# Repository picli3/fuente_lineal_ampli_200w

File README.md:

# fuente_lineal_ampli_200w

Fuente lineal diseñada para alimentar un amplificador de 200 W, con enfoque en robustez y compatibilidad con etapas de audio de potencia.

## Qué incluye
- esquemáticos o archivos de diseño en KiCad
- PCB o documentación asociada
- base reutilizable para análisis, fabricación o mejora del proyecto

## Propósito general
Este repositorio busca concentrar el diseño de hardware del proyecto en un formato editable y reutilizable, facilitando pruebas, documentación y futuras iteraciones del circuito.

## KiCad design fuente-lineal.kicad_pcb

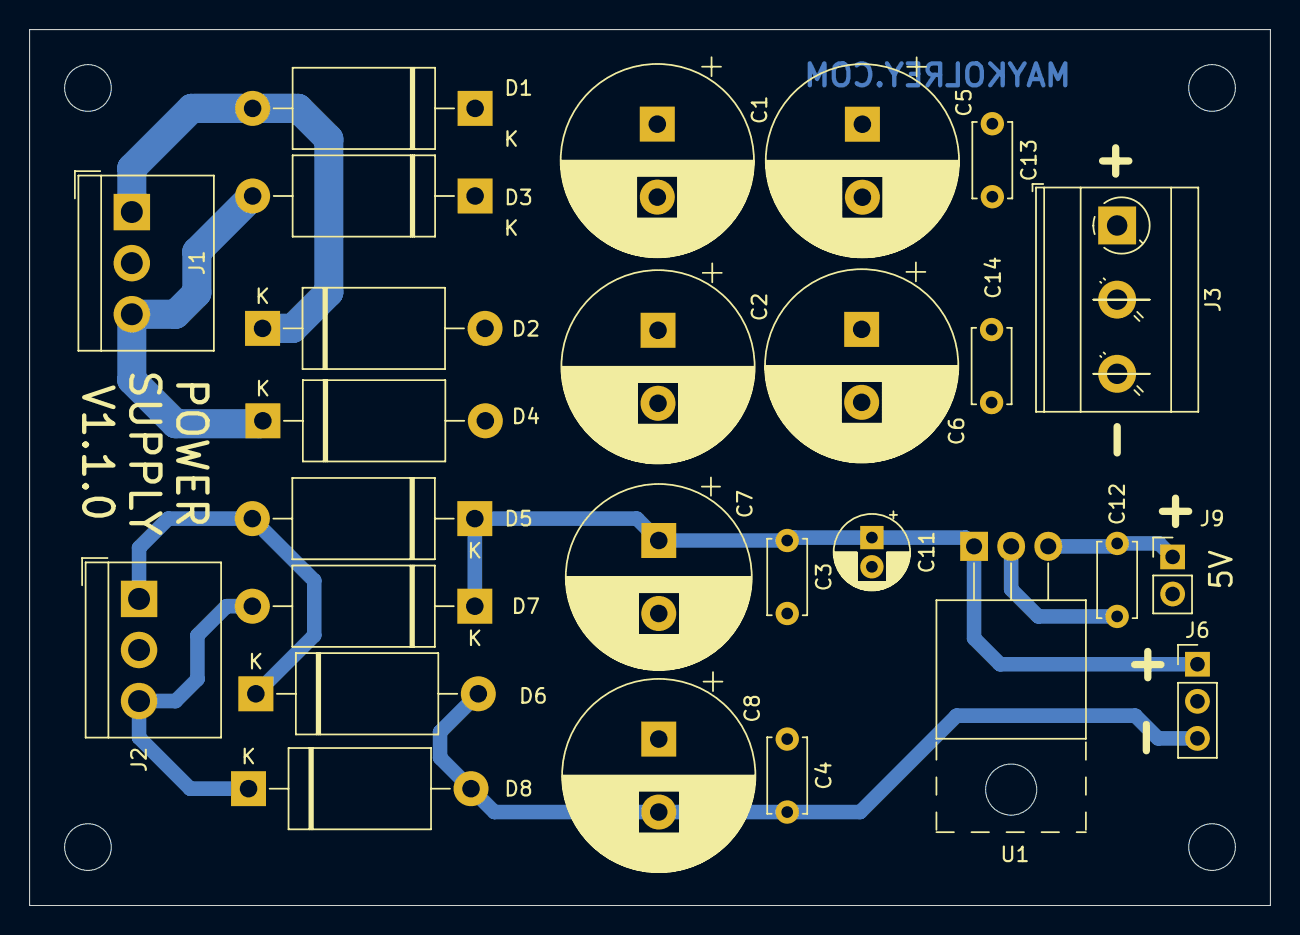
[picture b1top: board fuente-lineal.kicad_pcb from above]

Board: 2 copper layers, 85.0 x 60.0 mm, 30 parts (0 on the bottom side), 10 nets.

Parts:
C1, C2, C5, C6, C8: 2200uF; CP_Radial_D13.0mm_P5.00mm
C3, C4, C12, C13, C14: 100nF; C_Disc_D5.0mm_W2.5mm_P5.00mm
C7: 2200uF; CP_Radial_D12.5mm_P5.00mm
C11: 2.2uF; CP_Radial_D5.0mm_P2.00mm
D1, D2, D3, D4, D5, D6, D7, D8: 1N5404; D_DO-27_P15.24mm_Horizontal
H1, H2, H3, H4: MountingHole; MountingHole_3.2mm_M3
J1, J2: Conn_01x03; TerminalBlock_1x03_P3.50mm_Vertical
J3: Conn_01x03; TerminalBlock_MetzConnect_Type073_RT02603HBLU_1x03_P5.08mm_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
J6: Conn_01x03; PinHeader_1x03_P2.54mm_Vertical
J9: Conn_01x02; PinHeader_1x02_P2.54mm_Vertical
U1: LM7805_TO220; TO-220-3_Horizontal_TabUp

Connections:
/+5V: C12.1, J9.1, U1.3 (VO)
/V1i: D1.2 (A), D2.1 (K), J1.1
/V2i: D3.2 (A), D4.1 (K), J1.3
/V3i: D5.2 (A), D6.1 (K), J2.1
/V4i: D7.2 (A), D8.1 (K), J2.3
/Vo2n: C4.2, C8.2, D6.2 (A), D8.2 (A), J6.3
/Vo2p: C3.1, C7.1, C11.1, D5.1 (K), D7.1 (K), J6.1, U1.1 (VI)
/Von: C2.2, C6.2, C14.2, D2.2 (A), D4.2 (A), J3.3
/Vop: C1.1, C5.1, C13.1, D1.1 (K), D3.1 (K), J3.1
GND: C1.2, C2.1, C3.2, C4.1, C5.2, C6.1, C7.2, C8.1, C11.2, C12.2, C13.2, C14.1, J1.2, J2.2, J3.2, J6.2, J9.2, U1.2 (GND)

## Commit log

2023-05-07 primera version por fabricar
2023-12-17 completando version v1.1.0
2023-12-17 cambiando permisos de algunos archivos
2026-04-29 Agrega README con descripción inicial del proyecto
